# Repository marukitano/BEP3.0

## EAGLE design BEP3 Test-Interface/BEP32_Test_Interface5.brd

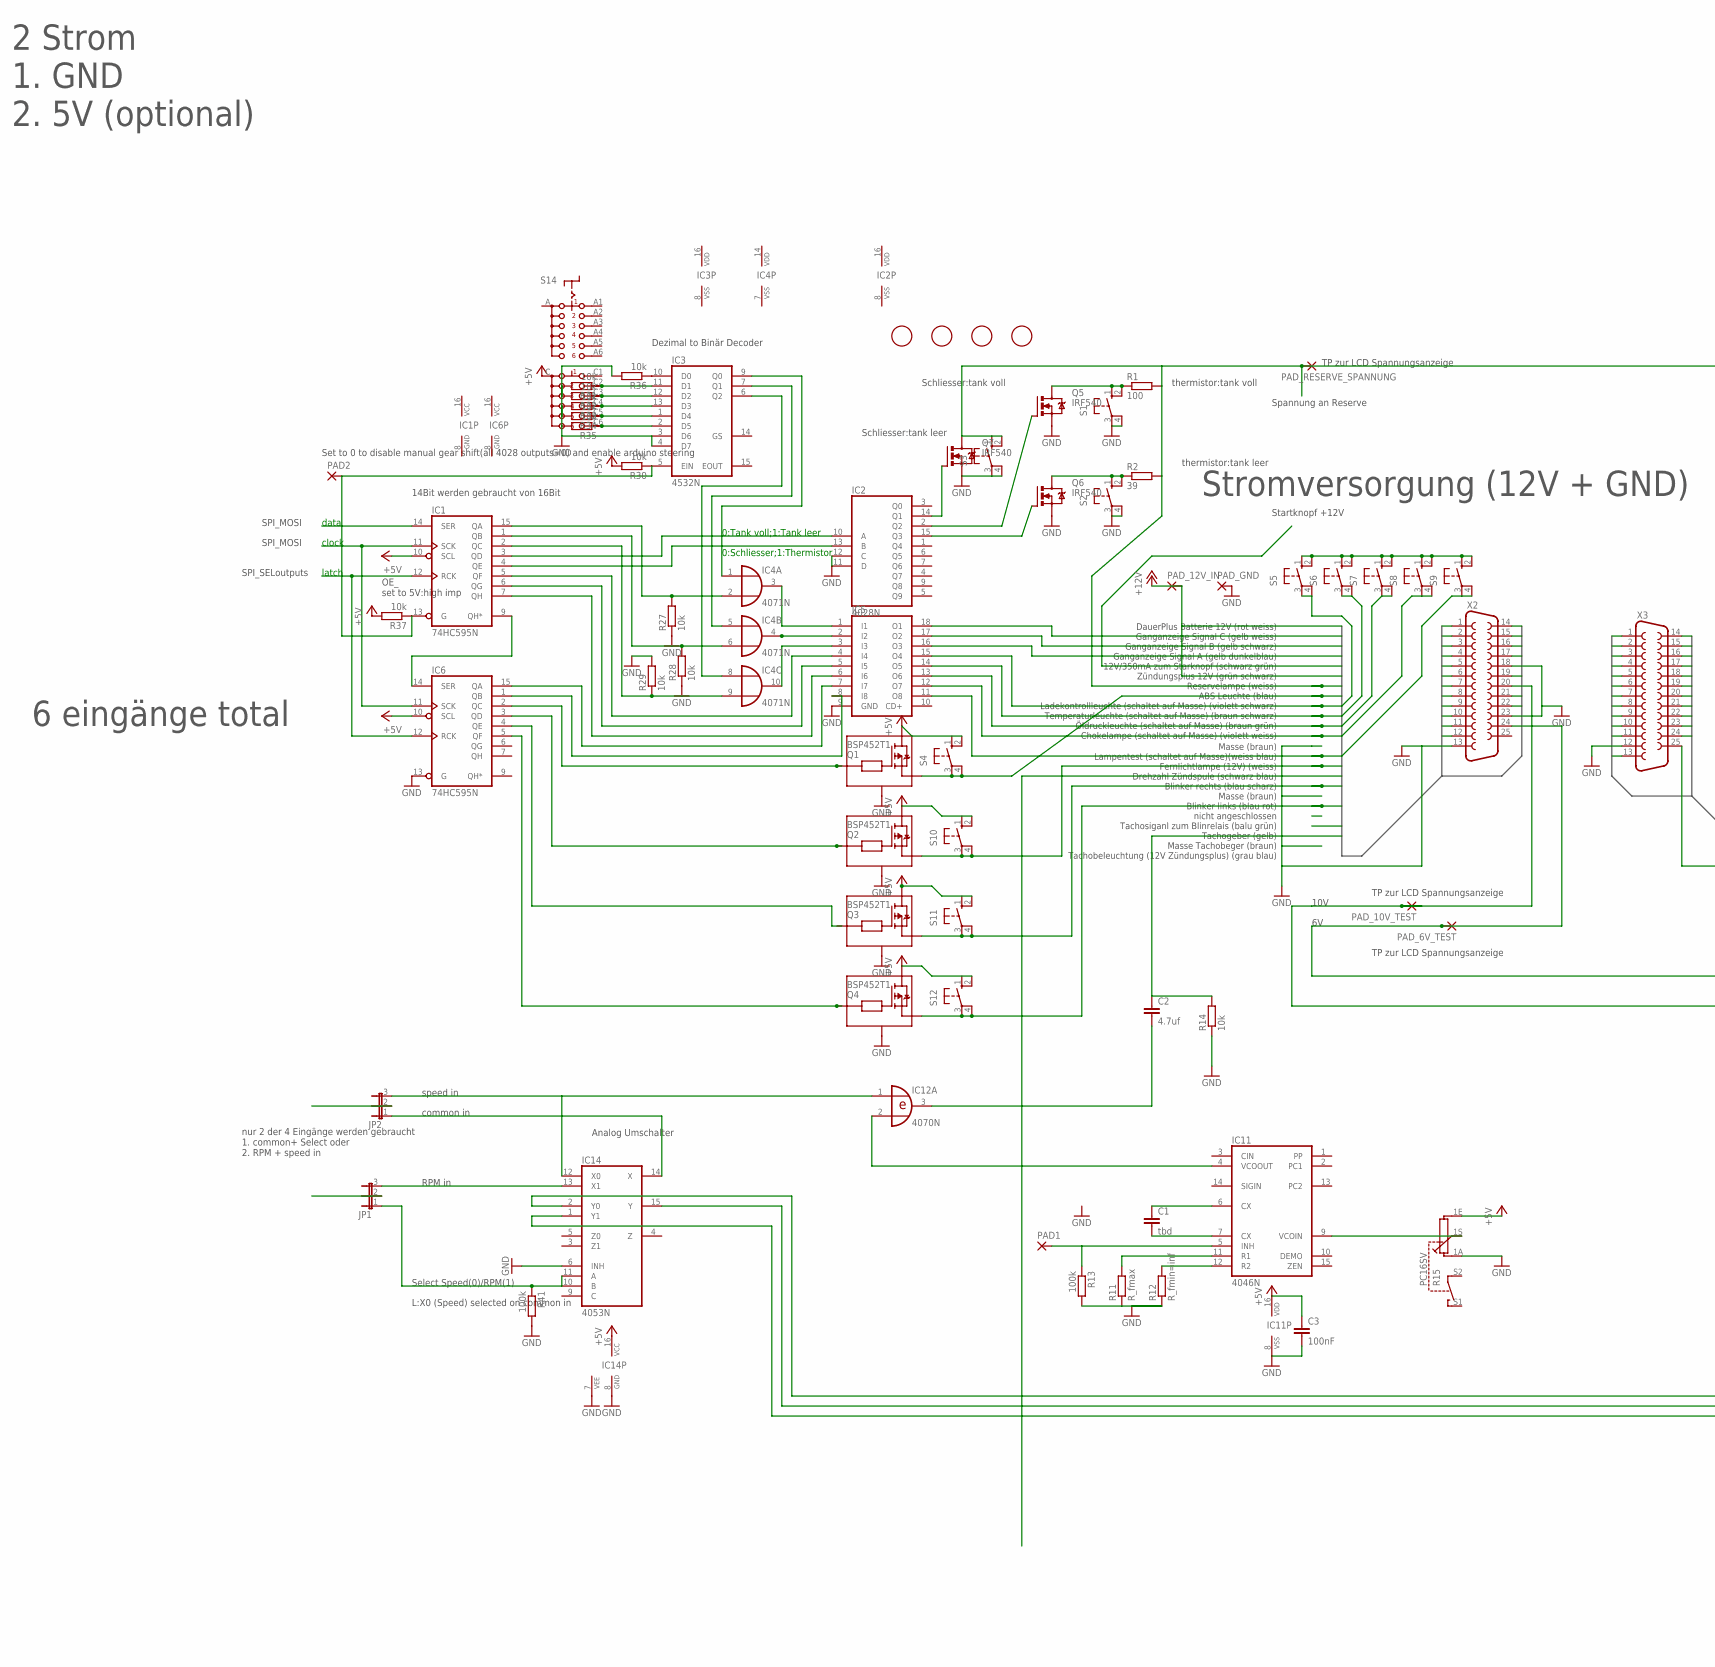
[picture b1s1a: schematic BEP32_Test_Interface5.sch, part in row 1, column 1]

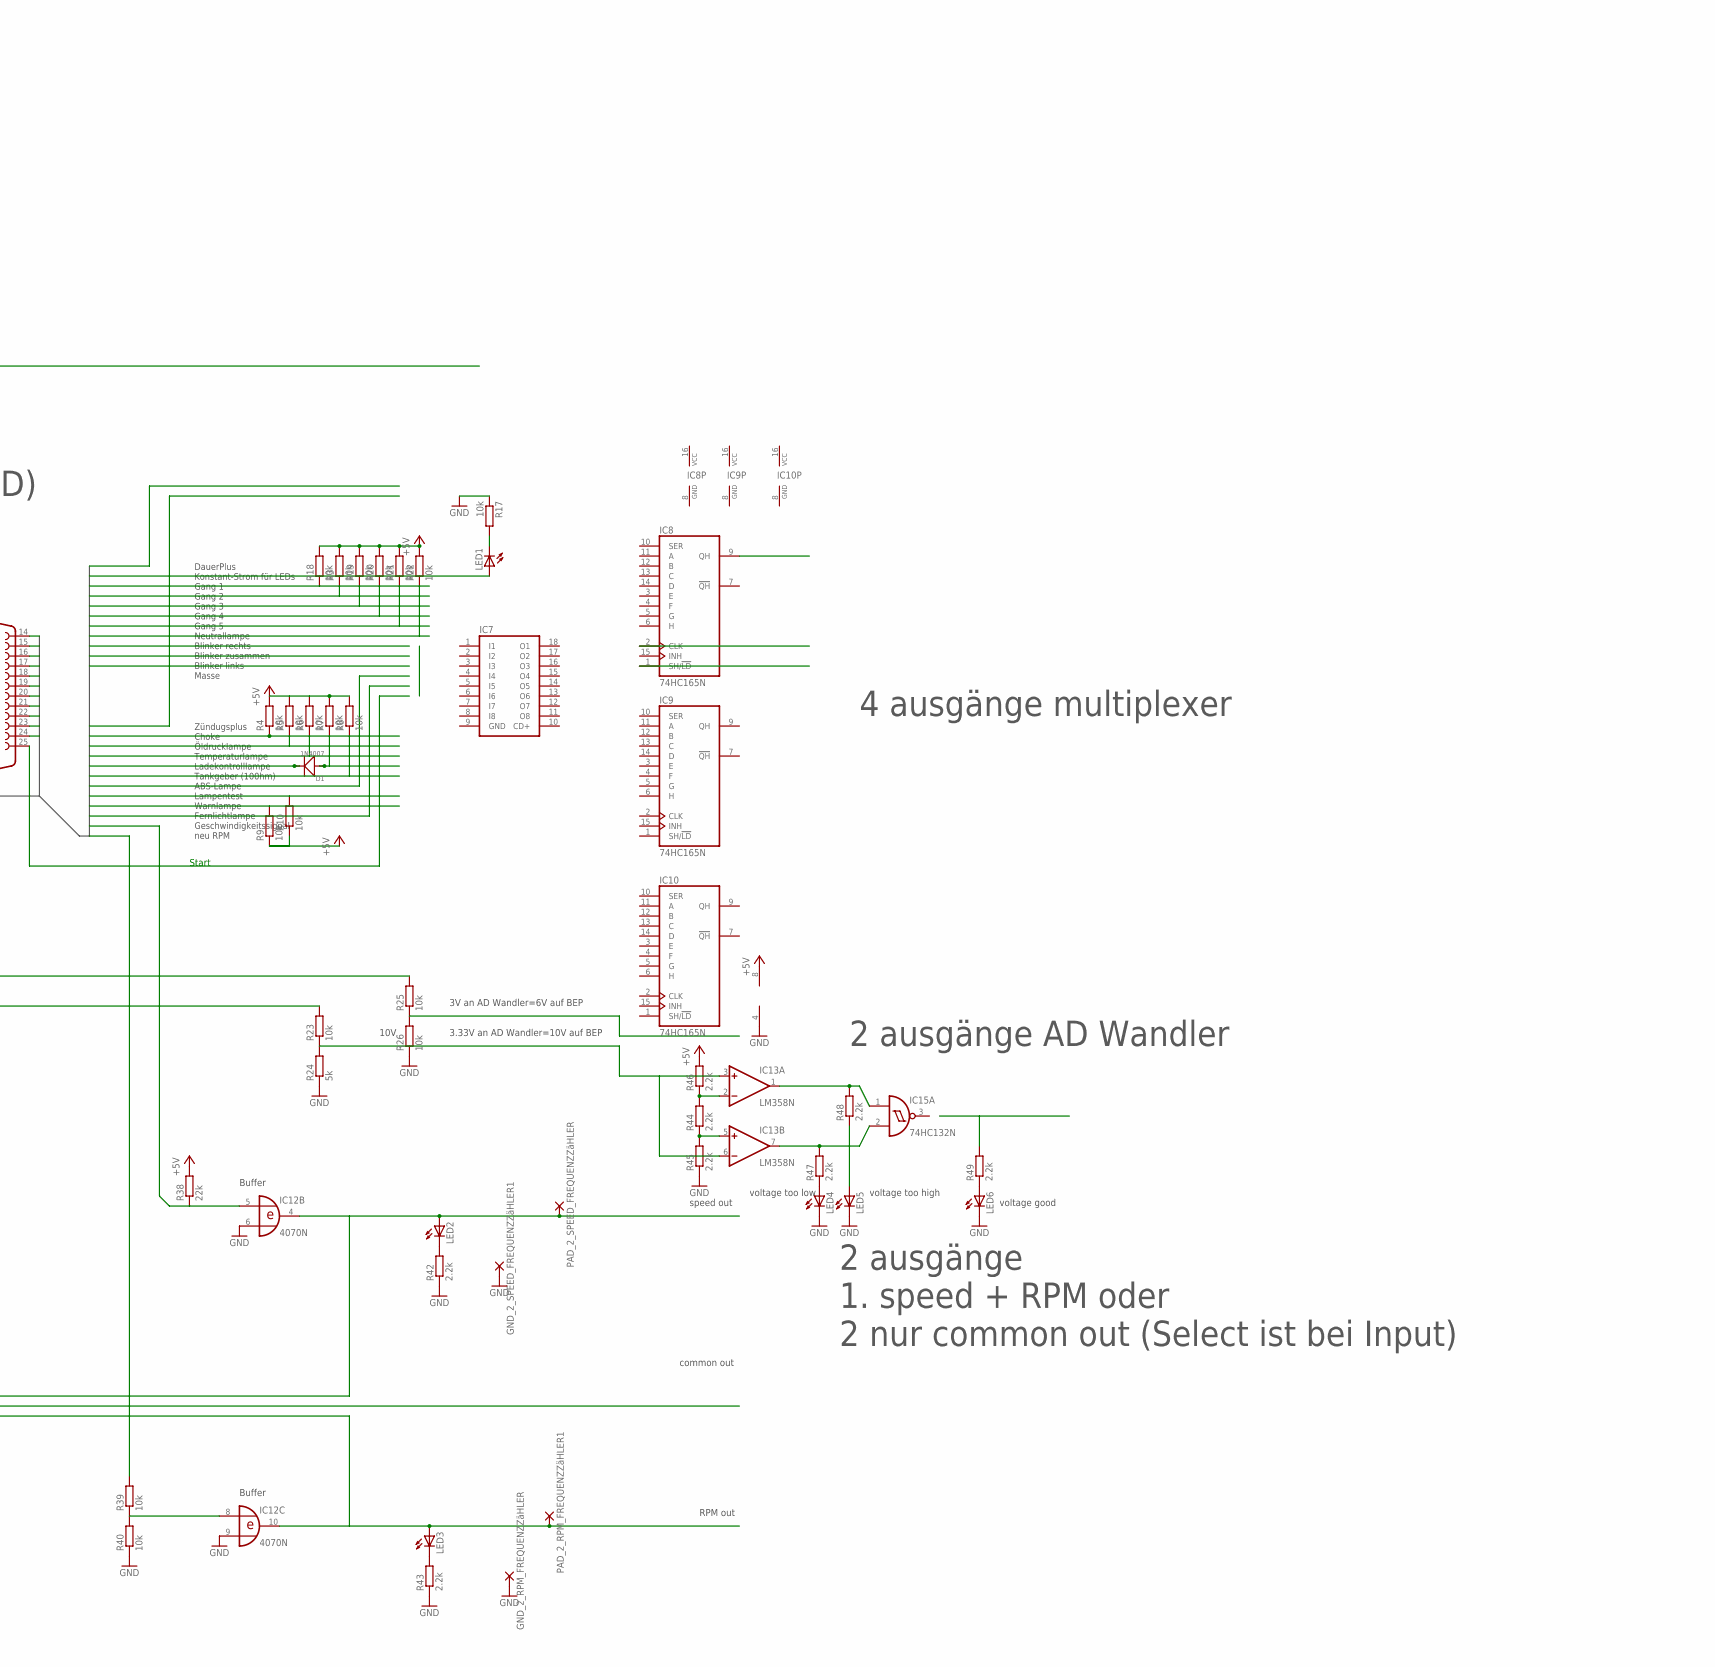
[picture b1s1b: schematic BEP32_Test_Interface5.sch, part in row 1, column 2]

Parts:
C1: tbd; C1206K
C2: 4.7uf; C025_050-025X075
C3: 100nF; C1206K
D1: 1N4007; DO-214AC
GND_2_RPM_FREQUENZZäHLER, GND_2_SPEED_FREQUENZZäHLER1: 1,6/0,9
IC1, IC6: 74HC595N; DIL16
IC2: 4028N; DIL16
IC3: 4532N; DIL16
IC4: 4071N; DIL14
IC5, IC7: ULN2803A; DIL18
IC8, IC9, IC10: 74HC165N; DIL16
IC11: 4046N; DIL16
IC12: 4070N; DIL14
IC13: LM358N; DIL08
IC14: 4053N; DIL16
IC15: 74HC132N; DIL14
JP1, JP2: JP2E; JP2
LED1, LED2, LED3, LED4, LED5, LED6: LED5MM
PAD1, PAD2: 1,6/0,9
PAD_2_RPM_FREQUENZZäHLER1, PAD_2_SPEED_FREQUENZZäHLER, PAD_6V_TEST, PAD_10V_TEST, PAD_12V_IN: 1,6/0,9
PAD_GND: 1,6/0,9
PAD_RESERVE_SPANNUNG: 1,6/0,9
Q1, Q2, Q3, Q4: BSP452T1; SOT223
Q5, Q6, Q7: IRF540; TO220BV
R1: 100; 0207/10
R2: 39; 0207/10
R3, R4, R5, R6, R7, R8, R9, R10, R14, R17, R18, R19, R20, R21, R22, R23, R25, R26, R27, R28, R29, R30, R31, R32, R33, R34, R35, R36, R37, R39, R40: 10k; 0207/10
R11: R_fmax; 0207/10
R12: R_fmin=inf; 0207/10
R13, R41: 100k; 0207/10
R15: PC16SV
R24: 5k; 0207/10
R38: 22k; 0207/10
R42, R43, R44, R45, R46, R47, R48, R49: 2.2k; 0207/10
S1, S2, S3, S4, S5, S6, S7, S8, S9, S10, S11, S12: 40-XX; B3F-40XX
S14: CK102X06
U$1, U$2, U$3, U$4: FIDUCIAL; FIDUCIAL_1MM
X2, X3: F25H

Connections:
+5V: C3.1, IC1.10 (SCL), IC6.10 (SCL), IC11.16 (VDD), IC13.8 (V+), IC14.16 (VCC), Q1.4 (V+), Q2.4 (V+), Q3.4 (V+), Q4.4 (V+), R3.2, R4.2, R5.2, R6.2, R7.2, R8.2, R9.1, R10.1, R15.1E, R18.2, R19.2, R20.2, R21.2, R22.2, R30.2, R37.2, R38.2, R46.2, S4.2 (S1), S10.2 (S1), S11.2 (S1), S12.2 (S1), S14.C
BMW1: PAD_12V_IN.1, X2.1
BMW2: IC5.18 (O1), X2.2
BMW3: IC5.17 (O2), X2.3
BMW4: IC5.16 (O3), X2.4
BMW5: X2.5
BMW6: X2.6
BMW7: PAD_RESERVE_SPANNUNG.1, Q7.D, R1.2, R2.2, S3.1 (S), S3.2 (S1), X2.7
BMW8: Q1.1 (OUT), S4.3, S4.4 (P1), X2.8
BMW9: IC5.15 (O4), S5.3, S5.4 (P1), X2.9
BMW10: IC5.14 (O5), S6.3, S6.4 (P1), X2.10
BMW11: IC5.13 (O6), S7.3, S7.4 (P1), X2.11
BMW12: IC5.12 (O7), S8.3, S8.4 (P1), X2.12
BMW14: IC5.11 (O8), S9.3, S9.4 (P1), X2.14
BMW15: Q2.1 (OUT), S10.3, S10.4 (P1), X2.15
BMW16: X2.16
BMW17: Q3.1 (OUT), S11.3, S11.4 (P1), X2.17
BMW19: Q4.1 (OUT), S12.3, S12.4 (P1), X2.19
BMW21: X2.21
BMW22: C2.1, R14.2, X2.22
BMW24: PAD_10V_TEST.1, R23.2, X2.20
GND: C3.2, GND_2_RPM_FREQUENZZäHLER.1, GND_2_SPEED_FREQUENZZäHLER1.1, IC1.8 (GND), IC2.11 (D), IC2.12 (C), IC3.3 (D6), IC3.4 (D7), IC5.9 (GND), IC6.8 (GND), IC6.13 (G), IC7.9 (GND), IC8.8 (GND), IC9.8 (GND), IC10.8 (GND), IC11.8 (VSS), IC12.6 (I1), IC12.9 (I1), IC13.4 (V-), IC14.6 (INH), IC14.7 (VEE), IC14.8 (GND), IC15.7 (GND), LED4.K (C), LED5.K (C), LED6.K (C), PAD_GND.1, Q1.2 (GND), Q2.2 (GND), Q3.2 (GND), Q4.2 (GND), Q5.S, Q6.S, Q7.S, R11.1, R12.1, R13.2, R14.1, R15.1A, R17.1, R24.1, R26.1, R27.1, R28.1, R29.2, R31.2, R32.2, R33.2, R34.2, R35.2, R36.2, R40.1, R41.2, R42.1, R43.1, R45.1, S1.3, S1.4 (P1), S2.3, S2.4 (P1), S3.3, S3.4 (P1), X2.13, X2.18, X2.23, X3.12
unnamed: Q6.D, R2.1, S2.1 (S), S2.2 (S1)
unnamed: Q5.D, R1.1, S1.1 (S), S1.2 (S1)
unnamed: IC2.2 (Q2), Q5.G
unnamed: IC2.14 (Q1), Q7.G
unnamed: IC4.3 (O), IC5.1 (I1)
unnamed: IC4.4 (O), IC5.2 (I2)
unnamed: IC4.10 (O), IC5.3 (I3)
unnamed: IC1.15 (QA), IC4.2 (I1), R27.2
unnamed: IC1.1 (QB), IC4.6 (I1), R28.2
unnamed: IC1.2 (QC), IC4.9 (I1), R29.1
unnamed: IC3.9 (Q0), IC4.1 (I0)
unnamed: IC3.7 (Q1), IC4.5 (I0)
unnamed: IC3.6 (Q2), IC4.8 (I0)
unnamed: IC1.3 (QD), IC2.10 (A)
unnamed: IC1.4 (QE), IC2.13 (B)
unnamed: IC1.9 (QH*), IC6.14 (SER)
unnamed: IC1.11 (SCK), IC6.11 (SCK)
unnamed: IC1.12 (RCK), IC6.12 (RCK)
unnamed: S5.1 (S), S5.2 (S1), S6.1 (S), S6.2 (S1), S7.1 (S), S7.2 (S1), S8.1 (S), S8.2 (S1), S9.1 (S), S9.2 (S1)
unnamed: IC1.5 (QF), IC5.4 (I4)
unnamed: IC1.6 (QG), IC5.5 (I5)
unnamed: IC1.7 (QH), IC5.6 (I6)
unnamed: IC5.7 (I7), IC6.15 (QA)
unnamed: IC5.8 (I8), IC6.1 (QB)
unnamed: IC6.2 (QC), Q1.3 (IN)
unnamed: IC6.3 (QD), Q2.3 (IN)
unnamed: IC6.5 (QF), Q4.3 (IN)
unnamed: C1.2, IC11.7 (CX)
unnamed: C1.1, IC11.6 (CX)
unnamed: IC11.11 (R1), R11.2
unnamed: IC11.12 (R2), R12.2
unnamed: C2.2, IC12.3 (O)
unnamed: IC11.4 (VCOOUT), IC12.2 (I1)
unnamed: IC11.5 (INH), PAD1.1, R13.1
unnamed: IC11.9 (VCOIN), R15.1S
unnamed: IC12.1 (I0), IC14.12 (X0), JP2.3
unnamed: D1.1 (+), R7.1
unnamed: LED1.K (C), R17.2
unnamed: R25.1, R26.2
unnamed: IC14.14 (X), JP2.1
unnamed: IC1.13 (G), IC3.5 (EIN), PAD2.1, R30.1, R37.1
unnamed: IC3.11 (D1), R31.1, S14.C2
unnamed: IC3.12 (D2), R32.1, S14.C3
unnamed: IC3.13 (D3), R33.1, S14.C4
unnamed: IC3.1 (D4), R34.1, S14.C5
unnamed: IC3.2 (D5), R35.1, S14.C6
unnamed: IC3.10 (D0), R36.1
unnamed: IC14.10 (B), IC14.11 (A), JP1.1, R41.1
unnamed: LED2.K (C), R42.2
unnamed: IC14.13 (X1), JP1.3
unnamed: IC12.8 (I0), R39.1, R40.2
unnamed: IC12.4 (O), IC14.2 (Y0), LED2.A, PAD_2_SPEED_FREQUENZZäHLER.1
unnamed: IC12.10 (O), IC14.1 (Y1), LED3.A, PAD_2_RPM_FREQUENZZäHLER1.1
unnamed: LED3.K (C), R43.2
unnamed: IC13.5 (+IN), R44.1, R45.2
unnamed: IC13.2 (-IN), R44.2, R46.1
unnamed: IC13.3 (+IN), IC13.6 (-IN), R23.1, R24.2
unnamed: IC13.1 (OUT), IC15.1 (I0), R48.2
unnamed: IC13.7 (OUT), IC15.2 (I1), R47.2
unnamed: LED4.A, R47.1
unnamed: LED5.A, R48.1
unnamed: LED6.A, R49.1
unnamed: PAD_6V_TEST.1, R25.2, X2.24
VCC: IC1.16 (VCC), IC6.16 (VCC), IC8.16 (VCC), IC9.16 (VCC), IC10.16 (VCC), IC15.14 (VCC)
VDD: IC2.16 (VDD), IC3.16 (VDD), IC4.14 (VDD), IC12.14 (VDD)
VSS: IC2.8 (VSS), IC3.8 (VSS), IC4.7 (VSS), IC12.7 (VSS)
WAGO1: X3.1
WAGO2: LED1.A, X3.2
WAGO3: R18.1, X3.3
WAGO4: R3.1, X3.4
WAGO5: R19.1, X3.5
WAGO6: R20.1, X3.6
WAGO7: R21.1, X3.7
WAGO8: R22.1, X3.8
WAGO9: X3.9
WAGO10: X3.10
WAGO11: X3.11
WAGO13: X3.13
WAGO14: R4.1, X3.14
WAGO15: R5.1, X3.15
WAGO16: R6.1, X3.16
WAGO17: D1.2 (-), X3.17
WAGO18: R8.1, X3.18
WAGO19: X3.19
WAGO20: R10.2, X3.20
WAGO21: R9.2, X3.21
WAGO22: X3.22
WAGO23: IC12.5 (I0), R38.1, X3.23
WAGO24: R39.2, X3.24

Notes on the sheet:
Zündugsplus Choke Öldrucklampe Temperaturlampe Ladekontrolllampe Tankgeber (100hm) ABS-Lampe Lampentest Warnlampe Fernlichtlampe Geschwindigkeitssignal neu RPM
DauerPlus Konstant-Strom für LEDs Gang 1 Gang 2 Gang 3 Gang 4 Gang 5 Neutrallampe Blinker rechts Blinker zusammen Blinker links Masse
DauerPlus Batterie 12V (rot weiss) Ganganzeige Signal C (gelb weiss) Ganganzeige Signal B (gelb schwarz) Ganganzeige Signal A (gelb dunkelblau) 12V/350mA zum Starknopf (schwarz grün) Zündungsplus 12V (grün schwarz) Reservelampe (weiss) ABS Leuchte (blau) Ladekontrollleuchte (schaltet auf Masse) (vi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
Masse (braun) Lampentest (schaltet auf Masse)(weiss blau) Fernlichtlampe (12V) (weiss) Drehzahl Zündspule (schwarz blau) Blinker rechts (blau scharz) Masse (braun) Blinker links (blau rot) nicht angeschlossen Tachosiganl zum Blinrelais (balu grün) Tachogeber (gelb) Masse Tachobeger (braun) Tachobel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
Start
10V
Dezimal to Binär Decoder
data
clock
OE_ set to 5V:high imp
latch
0:Tank voll;1:Tank leer
0:Schliesser;1:Thermistor
thermistor:tank leer
thermistor:tank voll
Schliesser:tank leer
Schliesser:tank voll
Startknopf +12V
14Bit werden gebraucht von 16Bit
Spannung an Reserve
3V an AD Wandler=6V auf BEP
3.33V an AD Wandler=10V auf BEP
TP zur LCD Spannungsanzeige
Set to 0 to disable manual gear shift(all 4028 outputs=0) and enable arduino steering
SPI_MOSI
SPI_SELoutputs
L:X0 (Speed) selected on common in
common in
speed in
RPM in
common out
speed out
Buffer
RPM out
Analog Umschalter
nur 2 der 4 Eingänge werden gebraucht 1. common+ Select oder 2. RPM + speed in
6 eingänge total
4 ausgänge multiplexer
2 ausgänge AD Wandler
2 ausgänge 1. speed + RPM oder 2 nur common out (Select ist bei Input)

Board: 2 copper layers, 112 parts (0 on the bottom side), 100 nets, no tracks yet.

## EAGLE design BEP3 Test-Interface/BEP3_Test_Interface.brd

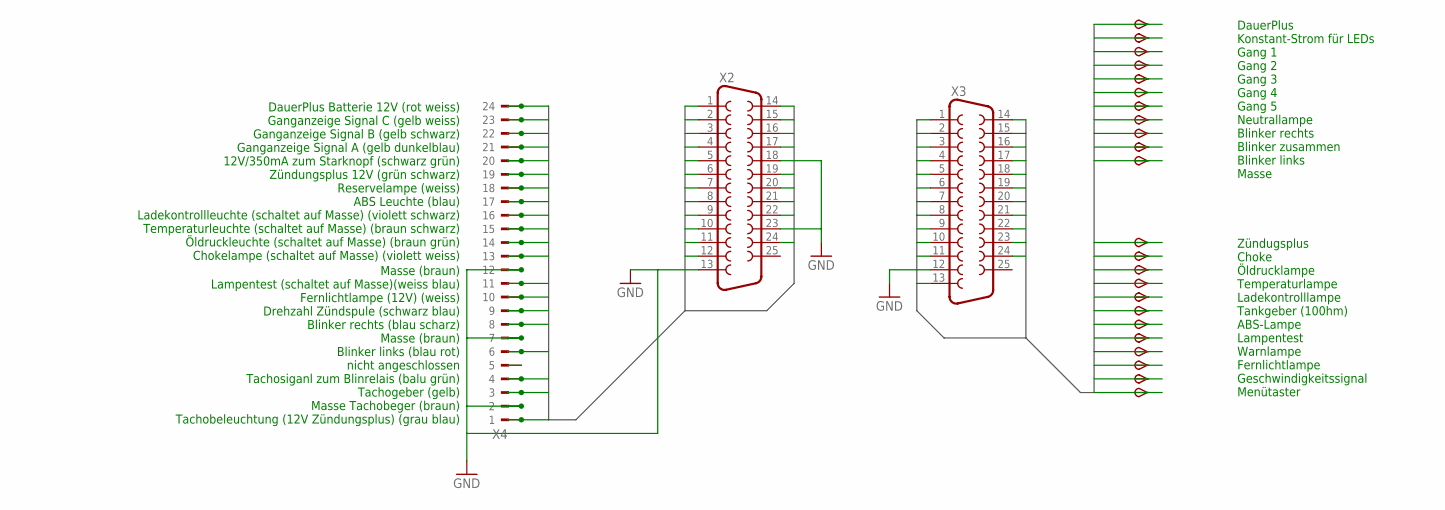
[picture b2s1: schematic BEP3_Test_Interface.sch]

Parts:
TP1, TP2, TP3, TP4, TP5, TP6, TP7, TP8, TP9, TP10, TP11, TP12, TP13, TP16, TP17, TP18, TP19, TP21, TP22, TP23, TP24, TP25, TP26: TPSFEDERPIN; 1,36ID
X2, X3: F25H
X4: CON_BMWTESTPINS; 24-TESTPIN_1,36ID

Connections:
BMW1: X2.1, X4.P24 (24)
BMW2: X2.2, X4.P23 (23)
BMW3: X2.3, X4.P22 (22)
BMW4: X2.4, X4.P21 (21)
BMW5: X2.5, X4.P20 (20)
BMW6: X2.6, X4.P19 (19)
BMW7: X2.7, X4.P18 (18)
BMW8: X2.8, X4.P17 (17)
BMW9: X2.9, X4.P16 (16)
BMW10: X2.10, X4.P15 (15)
BMW11: X2.11, X4.P14 (14)
BMW12: X2.12, X4.P13 (13)
BMW14: X2.14, X4.P11 (11)
BMW15: X2.15, X4.P10 (10)
BMW16: X2.16, X4.P9 (9)
BMW17: X2.17, X4.P8 (8)
BMW19: X2.19, X4.P6 (6)
BMW20: X2.20
BMW21: X2.21, X4.P4 (4)
BMW22: X2.22, X4.P3 (3)
BMW24: X2.24, X4.P1 (1)
GND: X2.13, X2.18, X2.23, X3.12, X4.P2 (2), X4.P7 (7), X4.P12 (12)
WAGO1: TP1.P$1, X3.1
WAGO2: TP2.P$1, X3.2
WAGO3: TP3.P$1, X3.3
WAGO4: TP4.P$1, X3.4
WAGO5: TP5.P$1, X3.5
WAGO6: TP6.P$1, X3.6
WAGO7: TP7.P$1, X3.7
WAGO8: TP8.P$1, X3.8
WAGO9: TP9.P$1, X3.9
WAGO10: TP10.P$1, X3.10
WAGO11: TP11.P$1, X3.11
WAGO13: TP12.P$1, X3.13
WAGO14: TP16.P$1, X3.14
WAGO15: TP17.P$1, X3.15
WAGO16: TP18.P$1, X3.16
WAGO17: TP19.P$1, X3.17
WAGO18: TP21.P$1, X3.18
WAGO19: TP22.P$1, X3.19
WAGO20: TP23.P$1, X3.20
WAGO21: TP24.P$1, X3.21
WAGO22: TP25.P$1, X3.22
WAGO23: TP26.P$1, X3.23
WAGO24: TP13.P$1, X3.24

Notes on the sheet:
Zündugsplus Choke Öldrucklampe Temperaturlampe Ladekontrolllampe Tankgeber (100hm) ABS-Lampe Lampentest Warnlampe Fernlichtlampe Geschwindigkeitssignal Menütaster
DauerPlus Konstant-Strom für LEDs Gang 1 Gang 2 Gang 3 Gang 4 Gang 5 Neutrallampe Blinker rechts Blinker zusammen Blinker links Masse
DauerPlus Batterie 12V (rot weiss) Ganganzeige Signal C (gelb weiss) Ganganzeige Signal B (gelb schwarz) Ganganzeige Signal A (gelb dunkelblau) 12V/350mA zum Starknopf (schwarz grün) Zündungsplus 12V (grün schwarz) Reservelampe (weiss) ABS Leuchte (blau) Ladekontrollleuchte (schaltet auf Masse) (vi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
Masse (braun) Lampentest (schaltet auf Masse)(weiss blau) Fernlichtlampe (12V) (weiss) Drehzahl Zündspule (schwarz blau) Blinker rechts (blau scharz) Masse (braun) Blinker links (blau rot) nicht angeschlossen Tachosiganl zum Blinrelais (balu grün) Tachogeber (gelb) Masse Tachobeger (braun) Tachobel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

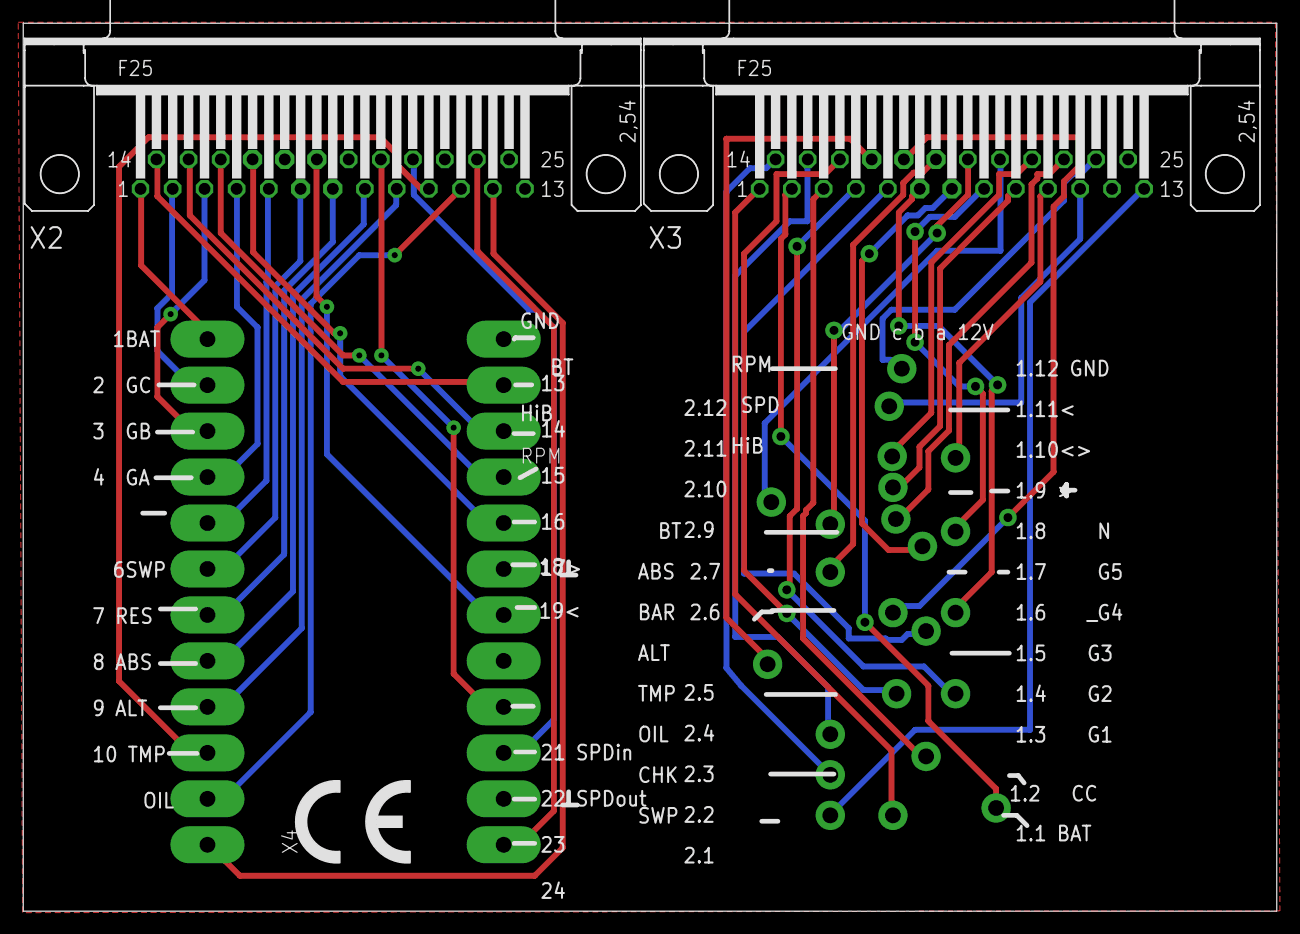
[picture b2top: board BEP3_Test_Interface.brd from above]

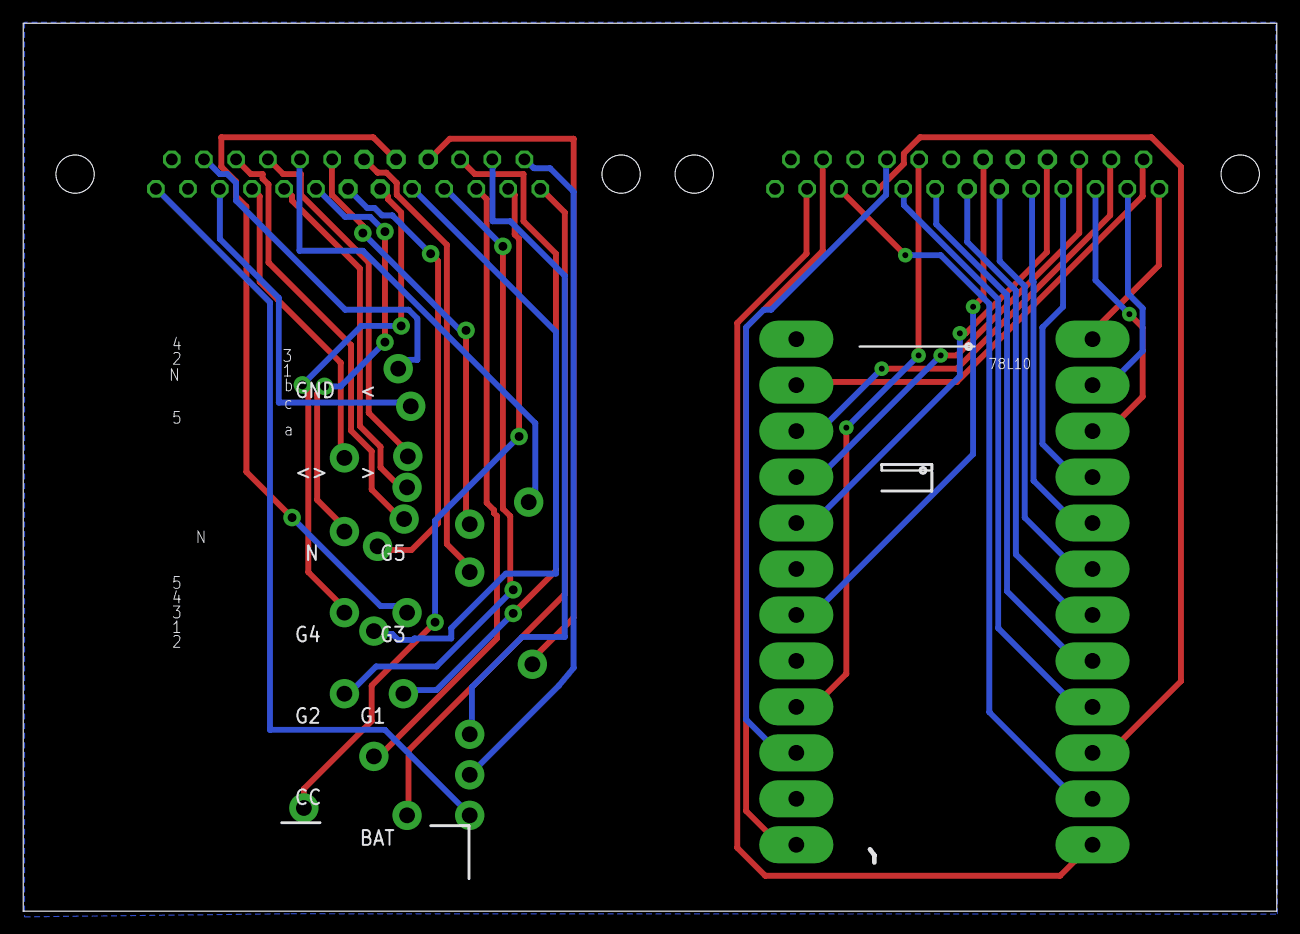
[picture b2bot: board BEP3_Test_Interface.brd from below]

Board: 2 copper layers, 108.0 x 76.5 mm, 27 parts (23 on the bottom side), 44 nets.

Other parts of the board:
U$1: CE_10.00

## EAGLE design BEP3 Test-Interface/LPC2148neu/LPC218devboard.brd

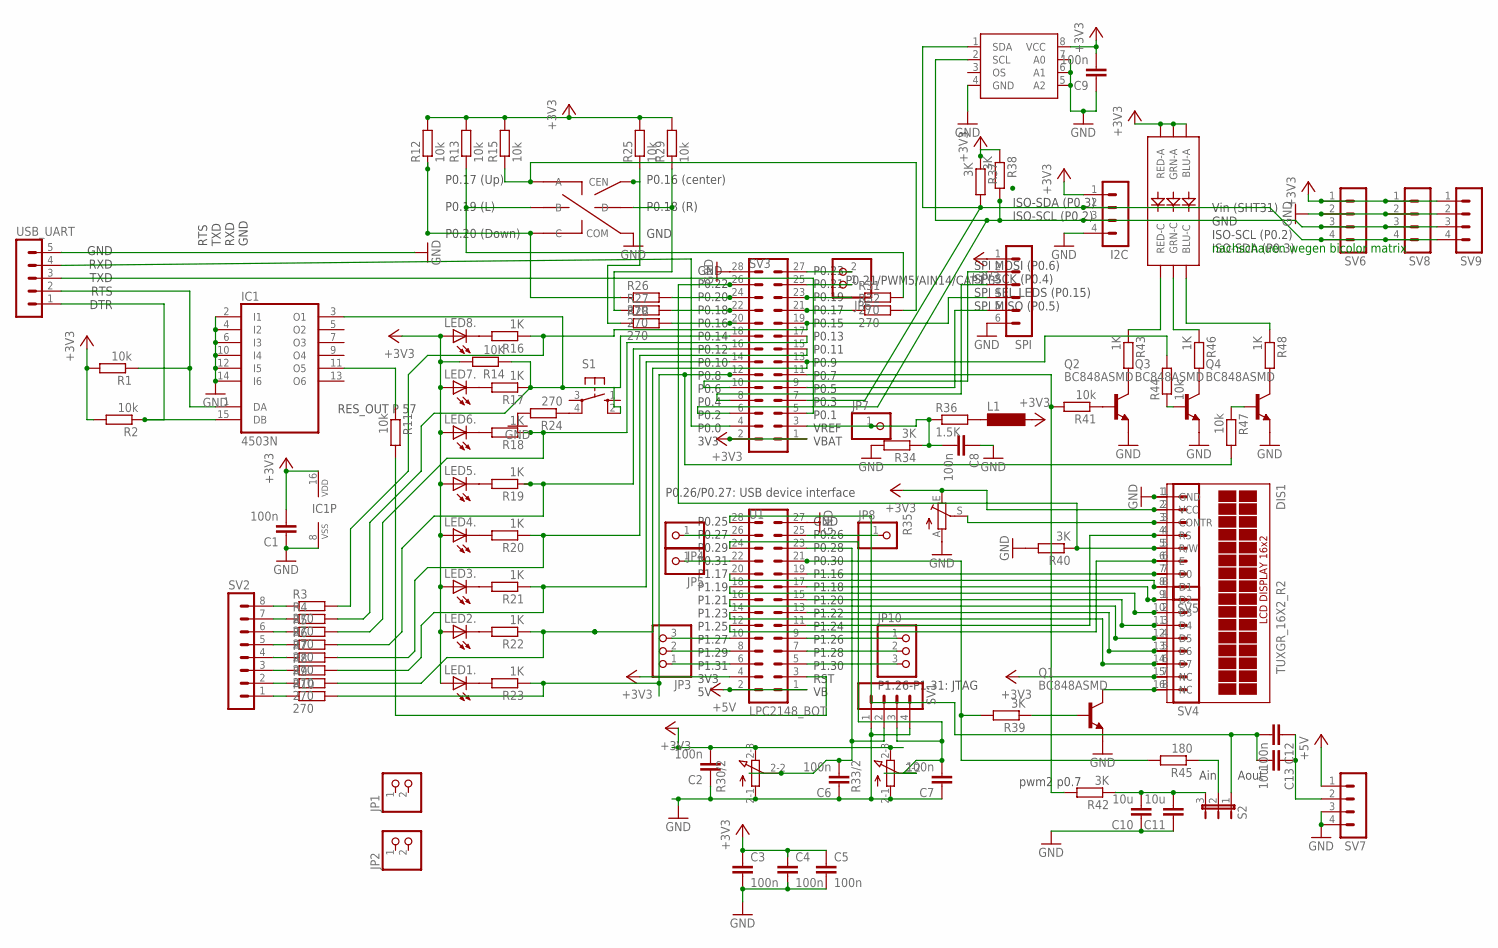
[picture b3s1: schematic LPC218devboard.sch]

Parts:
C1, C2, C3, C4, C5, C6, C7, C8, C9, C12: 100n; C0805
C10, C11, C13: 10u; C1206K
D1: LED-RGBNO_IC; LED-TRICOLOR-5050
DIS1: TUXGR_16X2_R2
I2C: MA04-1
IC1: 4503N; DIL16
IC2: LM75A; SO8
JP1, JP2, JP6: PINHD-1X2; 1X02
JP3, JP10: PINHD-1X3; 1X03
JP4, JP5, JP7, JP8: PINHD-1X1; 1X01
L1: MS50
LED1., LED2., LED3., LED4., LED5., LED6., LED7., LED8.: LED5MM
Q1, Q2, Q3, Q4: BC848ASMD; SOT23
R1, R2, R11, R12, R13, R15, R25, R29, R41, R44, R47: 10k; 0207/12
R3, R4, R5, R6, R7, R8, R9, R10: 270; R0805
R14: 10K; 0207/12
R16, R17: 1K; 0204/7
R18, R20: 1K; 0207/10
R19, R21, R22: 1K; 0207/12
R23: 1K; 0207/15
R24, R26, R27, R28, R31, R32: 270; 0207/12
R30, R33: DUAL_15MM_SHAFT; RK097G
R34, R42: 3K; 0207/12
R35: TRIM_EU-S63P; S63P
R36: 1.5K; 0207/10
R37, R38, R39, R40: 3K; R0805
R43, R46, R48: 1K; R0805
R45: 180; P0817/22
S1: 40-XX; B3F-40XX
S2: JP2E_ORIGJP2_ORIG; JP2_ORIG
SPI: MA06-1
SV1, SV6, SV7, SV8, SV9: MA04-1
SV2, SV4, SV5: MA08-1
SV3: LPC2148_TOP; ML26
SW1: ALPS_SKQ_MDSPTH; ALPS_SKQ_MDS_PTH
U1: LPC2148_BOT; ML26
USB_UART: MA05-1

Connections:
+3V3: C1.2, C2.2, C3.1, C4.1, C5.1, C9.2, D1.1 (GRN-A), D1.2 (RED-A), D1.3 (BLU-A), DIS1.2 (VCC), DIS1.15 (NC), I2C.1, IC1.16 (VDD), IC2.8 (VCC), L1.2, LED1..A, LED2..A, LED3..A, LED4..A, LED5..A, LED6..A, LED7..A, LED8..A, R1.2, R2.2, R12.2, R13.2, R14.2, R15.2, R25.2, R29.2, R30.2-3 (E), R33.2-3 (E), R35.E, R37.1, R38.1, SPI.1, SV3.1, SV3.2, SV4.7, SV5.2, SV6.1, SV8.1, SV9.1, U1.4
+5V: SV7.1, U1.1, U1.2
GND: C1.1, C2.1, C3.2, C4.2, C5.2, C6.1, C7.1, C8.1, C9.1, C10.1, C11.1, DIS1.1 (GND), I2C.4, IC1.2 (I1), IC1.4 (I2), IC1.6 (I3), IC1.8 (VSS), IC1.10 (I4), IC1.12 (I5), IC1.14 (I6), IC2.4 (GND), IC2.5 (A2), IC2.6 (A1), IC2.7 (A0), Q1.2 (E), Q2.2 (E), Q3.2 (E), Q4.2 (E), R24.2, R30.2-1 (A), R33.2-1 (A), R34.2, R35.A, R40.2, SPI.6, SV1.1, SV1.4, SV3.28, SV5.1, SV6.2, SV7.3, SV7.4, SV8.2, SV9.2, SW1.4 (COM), U1.27, USB_UART.5
unnamed: IC1.1 (DA), R1.1, USB_UART.2
unnamed: DIS1.7 (D0), SV5.7, U1.19
unnamed: DIS1.8 (D1), SV5.8, U1.20
unnamed: DIS1.9 (D2), SV4.1, U1.17
unnamed: DIS1.10 (D3), SV4.2, U1.18
unnamed: DIS1.11 (D4), SV4.3, U1.15
unnamed: DIS1.12 (D5), SV4.4, U1.16
unnamed: DIS1.13 (D6), SV4.5, U1.13
unnamed: R11.2, U1.3
unnamed: DIS1.5 (R/W), R40.1, SV3.26, SV5.5
unnamed: DIS1.6 (E), SV5.6, U1.12
unnamed: R39.2, R45.2, U1.21
unnamed: Q1.1 (B), R39.1
unnamed: DIS1.16 (NC), Q1.3 (C), SV4.8
unnamed: DIS1.3 (CONTR), R35.S, SV5.3
unnamed: R26.2, SV3.24
unnamed: R27.2, SV3.22
unnamed: R28.2, SV3.20
unnamed: R32.1, SV3.21
unnamed: R31.1, SV3.23
unnamed: R25.1, R28.1, SW1.6 (CEN)
unnamed: R27.1, R29.1, SW1.5 (D)
unnamed: R15.1, R32.2, SW1.1 (A)
unnamed: R13.1, R31.2, SW1.2 (B)
unnamed: R12.1, R26.1, SW1.3 (C)
unnamed: LED1..K (C), R23.2
unnamed: LED2..K (C), R22.2
unnamed: R24.1, S1.4 (P1)
unnamed: LED7..K (C), R17.2
unnamed: R3.1, SV2.8
unnamed: R4.1, SV2.7
unnamed: Q4.3 (C), R48.2
unnamed: LED3..K (C), R21.2
unnamed: LED4..K (C), R20.2
unnamed: R5.1, SV2.6
unnamed: R6.1, SV2.5
unnamed: R7.1, SV2.4
unnamed: Q3.3 (C), R46.2
unnamed: LED5..K (C), R19.2
unnamed: LED6..K (C), R18.2
unnamed: R8.1, SV2.3
unnamed: R9.1, SV2.2
unnamed: R10.1, SV2.1
unnamed: Q2.3 (C), R43.2
unnamed: LED8..K (C), R16.2
unnamed: L1.1, R36.2
unnamed: Q2.1 (B), R41.1
unnamed: D1.5 (RED-C), R43.1
unnamed: D1.6 (GRN-C), R46.1
unnamed: D1.4 (BLU-C), R48.1
unnamed: R41.2, R42.2, SV3.11
unnamed: Q4.1 (B), R47.1
unnamed: Q3.1 (B), R44.1
unnamed: SV3.4, USB_UART.4
unnamed: SV3.5, USB_UART.3
unnamed: C6.2, R30.2-2 (S), SV1.2, U1.23
unnamed: R45.1, S2.2
unnamed: C7.2, R33.2-2 (S), SV1.3, U1.24
unnamed: C12.1, C13.1, SV7.2
unnamed: C10.2, C11.2, R42.1, S2.3
unnamed: IC1.11 (O5), R11.1
unnamed: C12.2, C13.2, S2.1, U1.28
unnamed: IC1.15 (DB), R2.1, USB_UART.1
unnamed: C8.2, JP7.1, R34.1, R36.1, SV3.3
unnamed: JP10.1, U1.9
unnamed: JP10.2, U1.7
unnamed: JP10.3, U1.5
unnamed: JP3.3, U1.10
unnamed: JP3.2, U1.8
unnamed: JP3.1, U1.6
unnamed: JP4.1, U1.26
unnamed: JP5.1, U1.22
unnamed: JP8.1, U1.25
P0.8: R10.2, R23.1, R47.2, SV3.12
P0.9: R9.2, R22.1, R44.2, SV3.13
P0.10: R8.2, R21.1, SV3.14
P0.11: R7.2, R20.1, SV3.15
P0.12: R6.2, R19.1, SV3.16
P0.13: R5.2, R18.1, SV3.17
P0.14: IC1.3 (O1), R4.2, R14.1, R17.1, S1.2 (S1), SV3.18
P0.21: JP6.1, SV3.25
P0.23: JP6.2, SV3.27
P1.23: DIS1.14 (D7), SV4.6, U1.14
P1.24: DIS1.4 (RS), SV5.4, U1.11
SCL: I2C.3, IC2.2 (SCL), R38.2, SV3.6, SV6.3, SV8.3, SV9.3
SDA: I2C.2, IC2.1 (SDA), R37.2, SV3.7, SV6.4, SV8.4, SV9.4
SPI_MISO: SPI.5, SV3.9
SPI_MOSI: SPI.2, SV3.10
SPI_SCK: SPI.3, SV3.8
SPI_SEL: R3.2, R16.1, SPI.4, SV3.19

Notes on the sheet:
ISO-SDA (P0.3) ISO-SCL (P0.2)
SPI MOSI (P0.6) SPI SCK (P0.4) SPI SEL LEDS (P0.15) SPI MISO (P0.5)
RTS TXD RXD GND
pwm2 p0.7
Aout
Ain
GND RXD TXD RTS DTR
RES_OUT P 57
Vin (SHT31) GND ISO-SCL (P0.2) ISO-SDA (P0.3)
nachschauen wegen bicolor matrix
P0.26/P0.27: USB device interface
P1.26-P1.31: JTAG
P0.21/PWM5/AIN14/CAP1.3

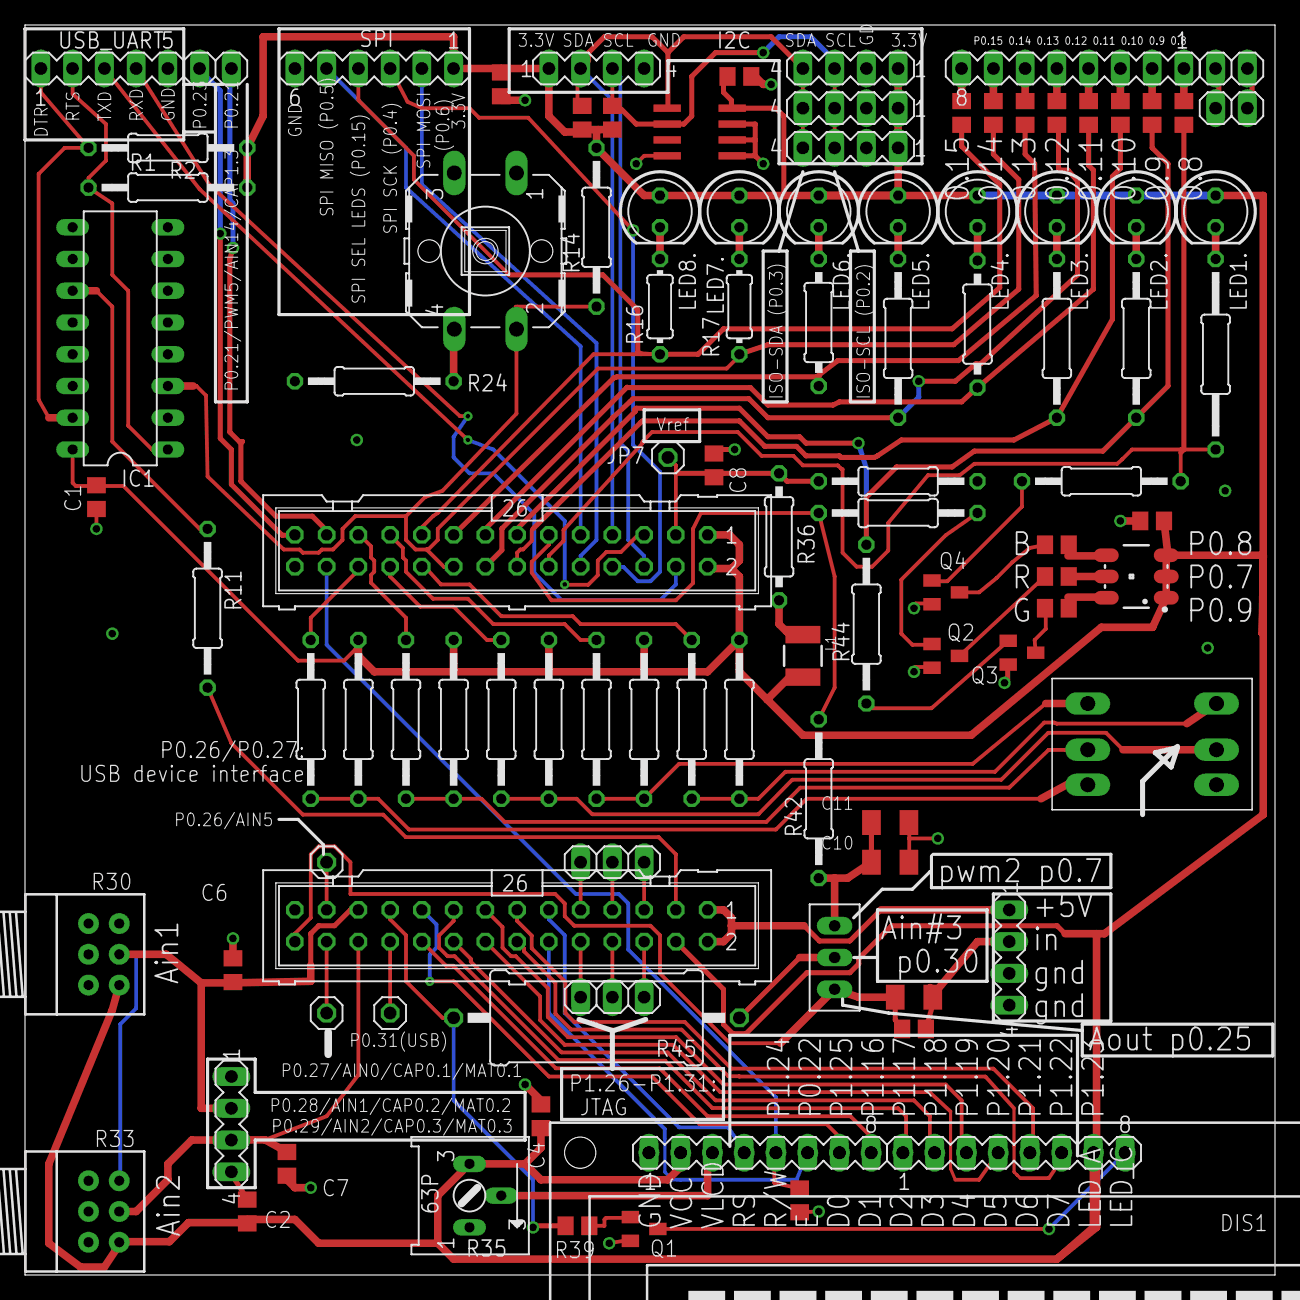
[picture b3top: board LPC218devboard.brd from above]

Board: 2 copper layers, 100.0 x 100.0 mm, 103 parts (0 on the bottom side), 93 nets.
